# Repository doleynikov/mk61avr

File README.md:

# mk61avr

**Эмулятор разбросан по файлам**

main.c

mk61types.h

vm61.c

vm61.h

vm61decoder.c

**есть служебные функции**

extlib.c - преобразования 16-ти ричной цифры в символ для печати;

	atoc() - ?;

	чтение-запись участка памяти из/в EEPROM;

**есть работа с аппаратурой**

keyboard.c - работа с клавиатурой как с устройством 

keyboard.h

lcd.c - работа с 16x2 LCD по параллельному интерфейсу

lcd.h

lowlevel.h

micro_os.h

scan_dc.c - преобразование сканкодов клавиатуры в ОПкоды 

store.c - работа с внешним i2c хранилищем

store.h

terminal.c - работа с калькулятором из терминала

terminal.h

time.c - ? работа с таймером. Вероятно для опроса клавиатуры

time.h

twi.c - TWI (i2C) функции для работы с внешним хранилищем

uart.c - библиотека функций для работы с последовательным портом

usart_module.h

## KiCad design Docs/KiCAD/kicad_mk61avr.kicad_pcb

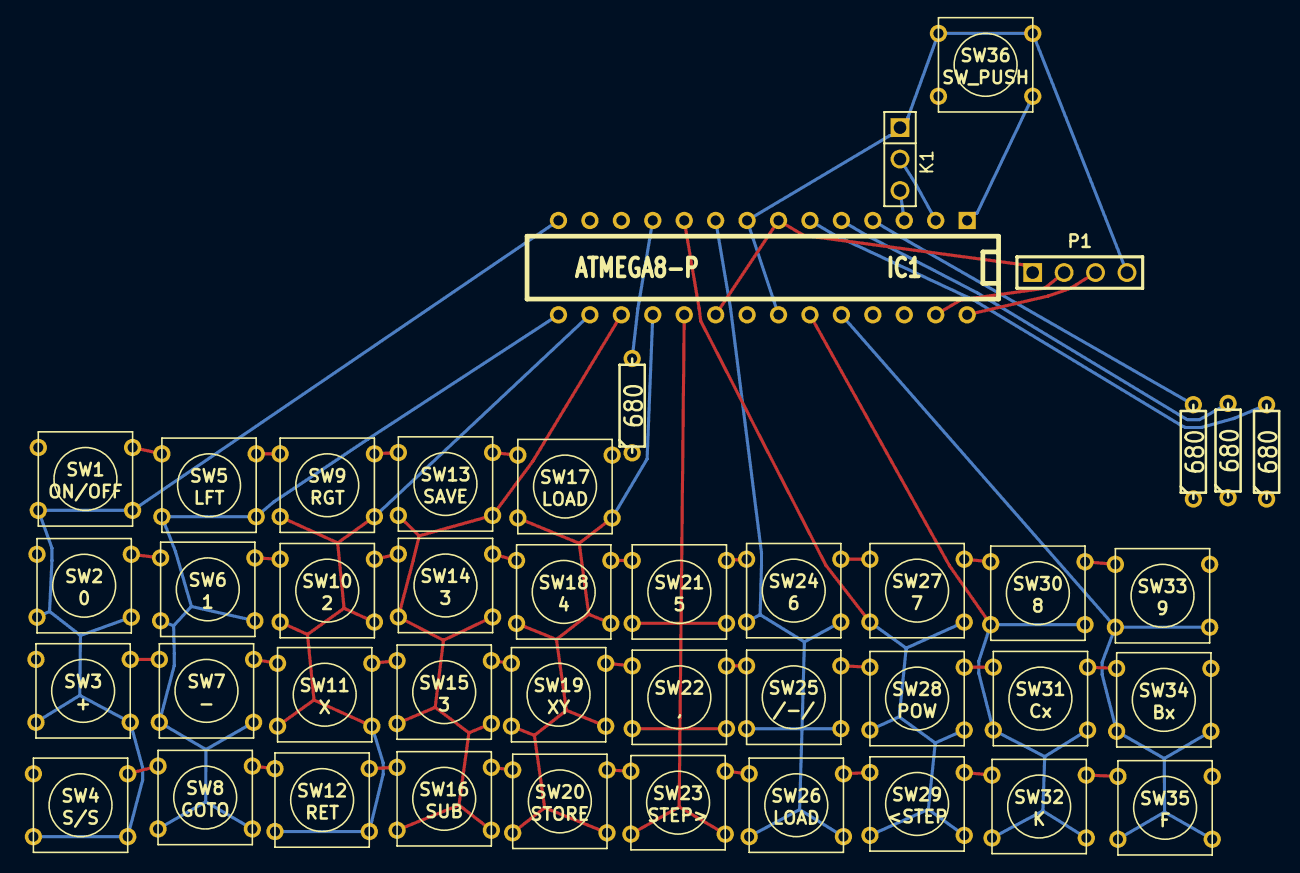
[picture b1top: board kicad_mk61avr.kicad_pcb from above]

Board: 2 copper layers, 43 parts (0 on the bottom side), 25 nets.

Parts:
IC1: ATMEGA8-P; DIP-28__300
K1: CONN_3; PIN_ARRAY_3X1
P1: CONN_4; PIN_ARRAY_4x1
R1, R2, R3, R4: 680; R3
SW1: ON/OFF; SW_PUSH_SMALL
SW2: 0; SW_PUSH_SMALL
SW3: +; SW_PUSH_SMALL
SW4: S/S; SW_PUSH_SMALL
SW5: LFT; SW_PUSH_SMALL
SW6: 1; SW_PUSH_SMALL
SW7: -; SW_PUSH_SMALL
SW8: GOTO; SW_PUSH_SMALL
SW9: RGT; SW_PUSH_SMALL
SW10: 2; SW_PUSH_SMALL
SW11: X; SW_PUSH_SMALL
SW12: RET; SW_PUSH_SMALL
SW13: SAVE; SW_PUSH_SMALL
SW14, SW15: 3; SW_PUSH_SMALL
SW16: SUB; SW_PUSH_SMALL
SW17, SW26: LOAD; SW_PUSH_SMALL
SW18: 4; SW_PUSH_SMALL
SW19: XY; SW_PUSH_SMALL
SW20: STORE; SW_PUSH_SMALL
SW21: 5; SW_PUSH_SMALL
SW22: ,; SW_PUSH_SMALL
SW23: STEP>; SW_PUSH_SMALL
SW24: 6; SW_PUSH_SMALL
SW25: /-/; SW_PUSH_SMALL
SW27: 7; SW_PUSH_SMALL
SW28: POW; SW_PUSH_SMALL
SW29: <STEP; SW_PUSH_SMALL
SW30: 8; SW_PUSH_SMALL
SW31: Cx; SW_PUSH_SMALL
SW32: K; SW_PUSH_SMALL
SW33: 9; SW_PUSH_SMALL
SW34: Bx; SW_PUSH_SMALL
SW35: F; SW_PUSH_SMALL
SW36: SW_PUSH; SW_PUSH_SMALL

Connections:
/COL_0: IC1.14, SW1.2, SW2.2, SW3.2, SW4.2
/COL_1: IC1.15, SW5.2, SW6.2, SW7.2, SW8.2
/COL_2: IC1.16, SW9.2, SW10.2, SW11.2, SW12.2
/COL_3: IC1.17, SW13.2, SW14.2, SW15.2, SW16.2
/COL_4: IC1.18, SW17.2, SW18.2, SW19.2, SW20.2
/COL_5: IC1.19, SW21.2, SW22.2, SW23.2
/COL_6: IC1.9, SW24.2, SW25.2, SW26.2
/COL_7: IC1.10, SW27.2, SW28.2, SW29.2
/COL_8: IC1.23, SW30.2, SW31.2, SW32.2
/COL_9: IC1.24, SW33.2, SW34.2, SW35.2
/I2C_SCL: IC1.28, P1.3
/I2C_SDA: IC1.27, P1.2
/ROW_0: IC1.4, R2.2
/ROW_1: IC1.5, R3.2
/ROW_2: IC1.6, R4.2
/ROW_3: IC1.11, R1.2
/RX: IC1.2, K1.2
/TX: IC1.3, K1.3
GND: IC1.8, IC1.22, K1.1, P1.4, SW36.1
unnamed: R3.1, SW3.1, SW7.1, SW11.1, SW15.1, SW19.1, SW22.1, SW25.1, SW28.1, SW31.1, SW34.1
unnamed: IC1.1, SW36.2
unnamed: R4.1, SW4.1, SW8.1, SW12.1, SW16.1, SW20.1, SW23.1, SW26.1, SW29.1, SW32.1, SW35.1
unnamed: R1.1, SW1.1, SW5.1, SW9.1, SW13.1, SW17.1
unnamed: R2.1, SW2.1, SW6.1, SW10.1, SW14.1, SW18.1, SW21.1, SW24.1, SW27.1, SW30.1, SW33.1
VCC: IC1.7, IC1.20, P1.1

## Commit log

2017-01-13 PDFs
2017-01-13 Commit from ECLIPSE
2017-01-13 Added CFLAGS += -D__AVR_LIBC_DEPRECATED_ENABLE__ to makefile
2017-01-13 Headers of some sources updated
2017-01-14 Source files converted to UTF8
2017-01-14 Main file converted to utf8
2017-01-16 latest fzz
2017-01-16 Recover FZZ
2017-01-16 FZZ: USBASP added
2017-01-16 FZZ: I2C and UART added
2017-01-16 FZZ: updated
2017-01-17 KiCAD:added schematic
2017-01-17 KiCAD:some editing
2017-01-18 KiCAD:PCB design from TopoR
2017-01-18 Подправлены комментарии и изменен readme для github
2017-01-18 README corrected
2017-01-18 USBASP plug added to schematics
2017-01-18 MK61 manual added
2017-01-19 Kikad files added
2017-01-19 Readme.md
2017-01-19 KiCAD: обновил схему от Алексея
2017-01-20 Обновил README
2017-01-24 KICAD: переделал схему клавиатуры под матрицу 5x8
2017-01-25 пилил исходники
2017-01-25 пилил исходники1
2017-01-31 схема
2017-01-31 KICAD: arduino added
2017-01-31 hwTest sketch added
2017-02-01 hwTest keymap corrected
2017-02-02 hwTest: comment added
2017-02-02 KiCAD: PDF added
2017-02-02 hwTest: comment changed
2017-02-06 Added simple BASIC interpreter :-)
2017-02-08 эксперимент с драйвером клавиатуры по таймеру - разобраться с повторными нажатиями
2017-02-10 эксперименты
2017-02-14 bit-op : almost working keyboard
2017-02-14 bit-op : some corrections
2017-03-01 чистка репозитория
2017-03-01 небольшие исправления
2017-03-02 п÷я─п╬п╠я┐я▌ п╢п╬п©п╦я│п╟я┌я▄ я│п╡п╬п╧ я█п╪п╦я┌п╟я┌п╬я─
2017-03-02 п╢п╬я─п╟п╠п╬я┌п╨п╦
2017-03-03 п©я─п╬п╢п╬п╩п╤п╣п╫п╦п╣
2017-03-24 KBtest
2017-03-27 п▓я─п╬п╢п╣ я─п╟п╠п╬я┌п╟п╣я┌ п╨п╩п╟п╡п╦п╟я┌я┐я─п╟
2017-03-30 SPI-SRAM test added (avr-gcc Makefile)
2017-03-30 Makefile updated
2017-03-30 Typo fixed
2017-03-31 Sources splitted, new Makefile
2017-03-31 Combined LCD-SRAM HW test added
2017-04-01 Serial console disabled in SRAM-LCD test
2017-04-02 avrgcc version of i2c LCD test added
2017-04-02 LCD pins are corrected
2017-04-03 Cosmetic fix
